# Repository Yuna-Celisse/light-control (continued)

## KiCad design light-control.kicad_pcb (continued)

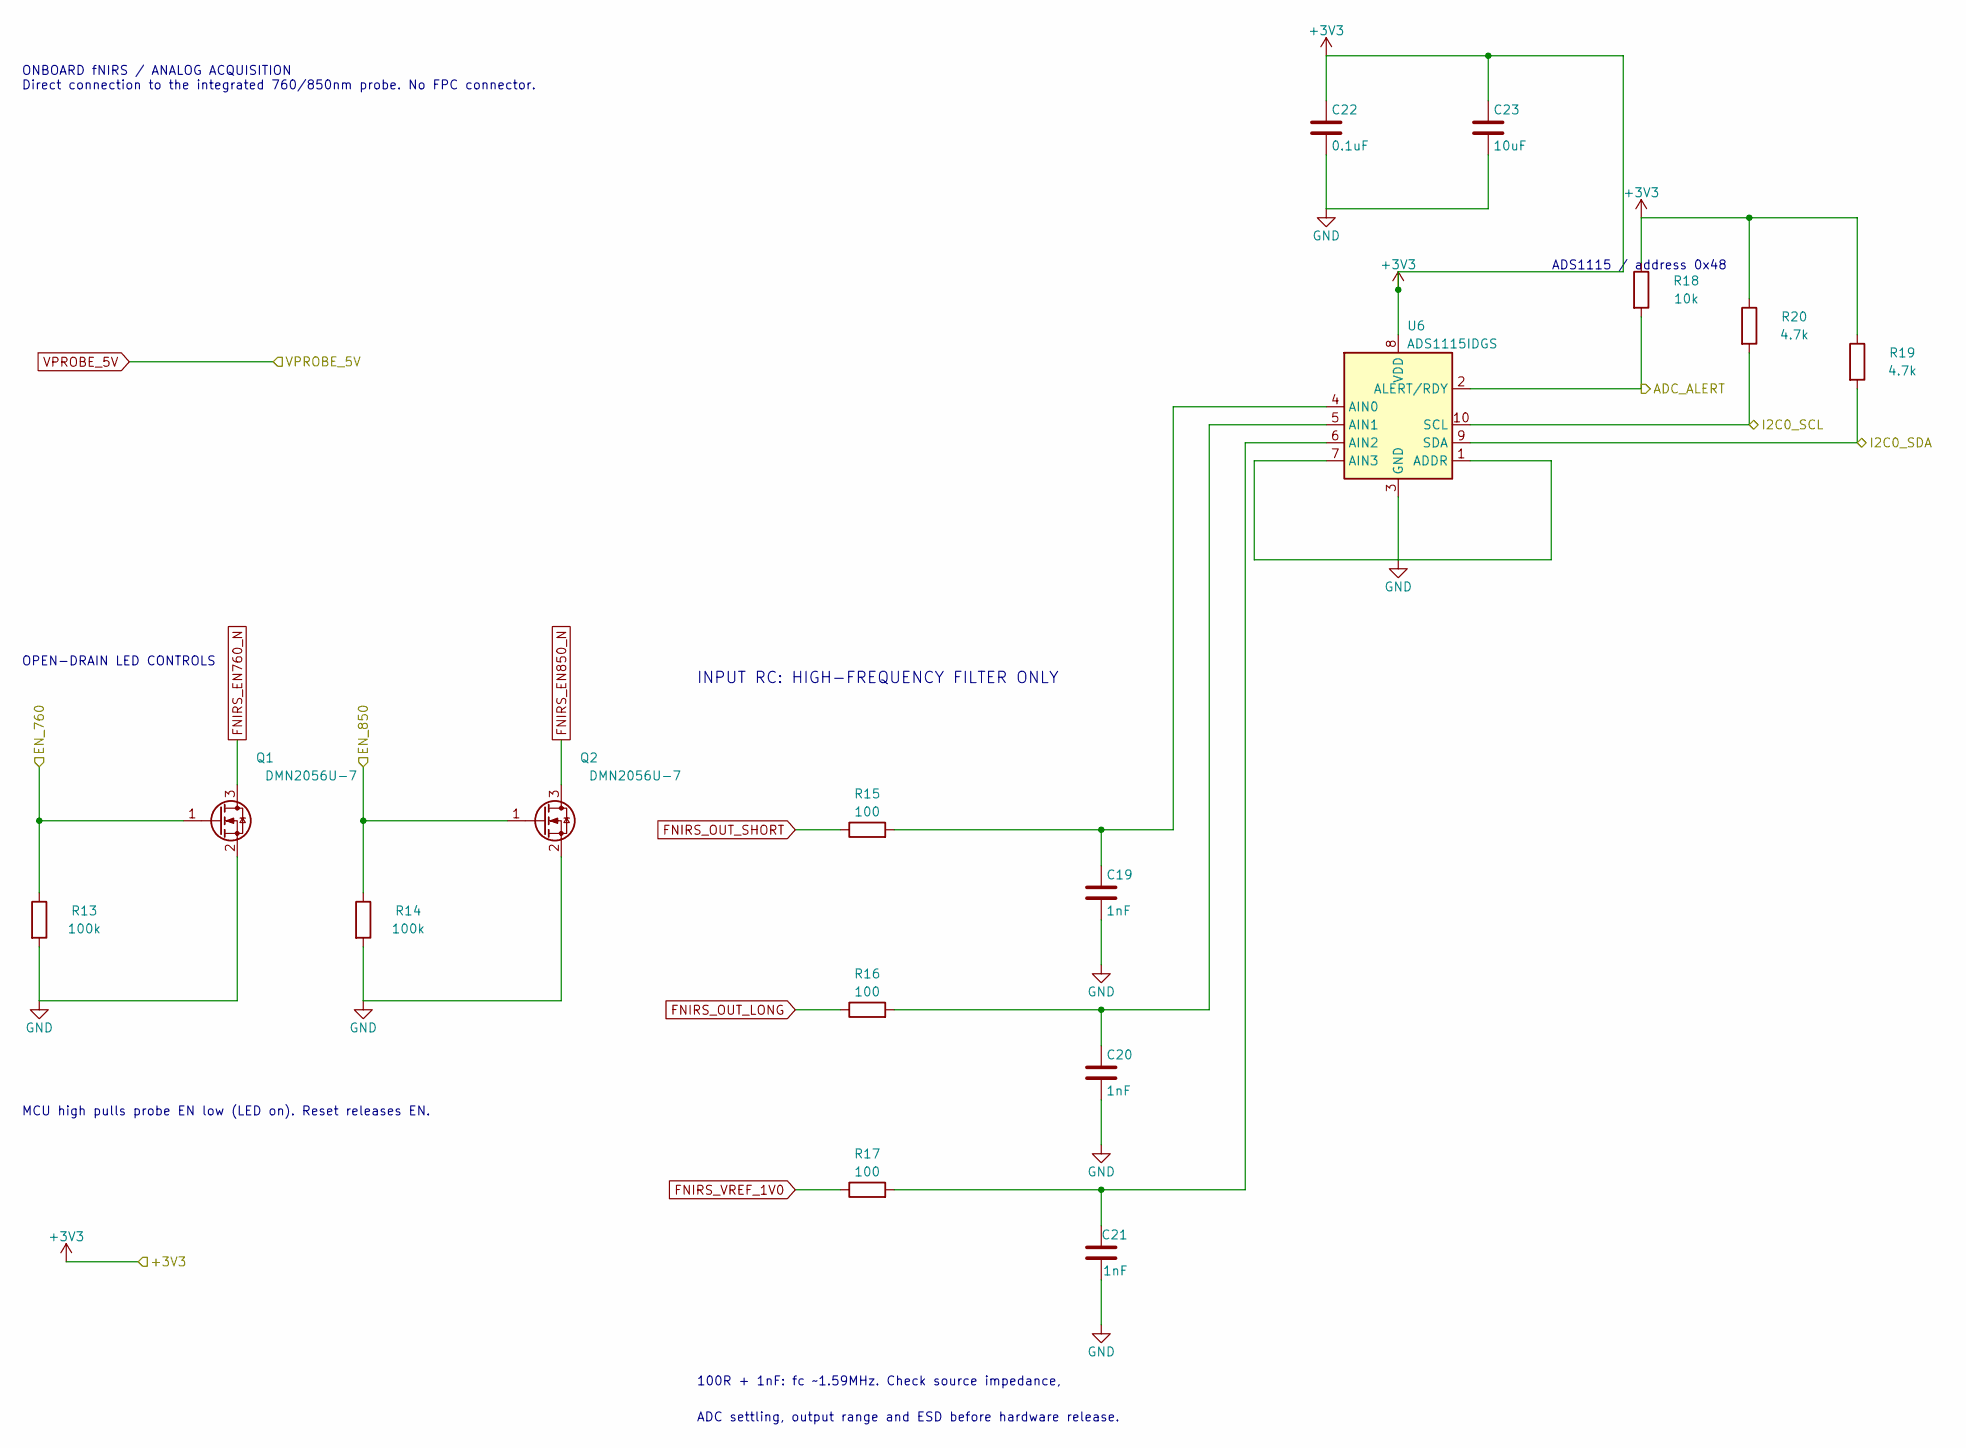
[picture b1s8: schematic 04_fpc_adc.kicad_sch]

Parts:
C19, C20, C21: 1nF; C_0402_1005Metric
C22: 0.1uF; C_0402_1005Metric
C23: 10uF; C_0805_2012Metric
Q1, Q2: DMN2056U-7; SOT-23; MPN DMN2056U-7
R13, R14: 100k; R_0402_1005Metric
R15, R16, R17: 100; R_0402_1005Metric
R18: 10k; R_0402_1005Metric
R19, R20: 4.7k; R_0402_1005Metric
U6: ADS1115IDGS; TSSOP-10_3x3mm_P0.5mm; MPN ADS1115IDGS

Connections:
+3V3: C22.1, C23.1, R18.1, R19.1, R20.1, U6.8 (VDD); also elsewhere on the board
/ADC_ALERT: R18.2, U6.2 (ALERT/RDY); also elsewhere on the board
/EN_760: Q1.1 (G), R13.1; also elsewhere on the board
/EN_850: Q2.1 (G), R14.1; also elsewhere on the board
/I2C0_SCL: R20.2, U6.10 (SCL); also elsewhere on the board
/I2C0_SDA: R19.2, U6.9 (SDA); also elsewhere on the board
FNIRS_EN760_N: Q1.3 (D); also elsewhere on the board
FNIRS_EN850_N: Q2.3 (D); also elsewhere on the board
FNIRS_OUT_LONG: R16.1; also elsewhere on the board
FNIRS_OUT_SHORT: R15.1; also elsewhere on the board
FNIRS_VREF_1V0: R17.1; also elsewhere on the board
unnamed: C19.1, R15.2, U6.4 (AIN0)
unnamed: C20.1, R16.2, U6.5 (AIN1)
unnamed: C21.2, R17.2, U6.6 (AIN2)

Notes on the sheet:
ADC settling, output range and ESD before hardware release.
ADS1115 / address 0x48
100R + 1nF: fc ~1.59MHz. Check source impedance,
INPUT RC: HIGH-FREQUENCY FILTER ONLY
MCU high pulls probe EN low (LED on). Reset releases EN.
ONBOARD fNIRS / ANALOG ACQUISITION Direct connection to the integrated 760/850nm probe. No FPC connector.
OPEN-DRAIN LED CONTROLS

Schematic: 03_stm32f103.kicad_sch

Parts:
C15: 10uF; C_0805_2012Metric
C16, C17, C18, C33, C35, C37: 100nF; C_0402_1005Metric
C34: 1uF; C_0402_1005Metric
C38, C39: 6pF C0G; C_0402_1005Metric
D1: LED_STATE; LED_0603_1608Metric
J2: SWD_PADS; SWD_SolderPads_1x06_P2.00mm
R9, R11, R12, R41: 10k; R_0402_1005Metric
R10: 1k; R_0402_1005Metric
R36, R37: 22; R_0402_1005Metric
R42: 1.5k; R_0402_1005Metric
SW1: RESET; SW_SPST_PTS645Sx43SMTR92
SW2: USER_KEY; SW_SPST_PTS645Sx43SMTR92
SW3: BOOT; SW_SPST_PTS645Sx43SMTR92
TP1: USART1_RX; TestPoint_Pad_D1.0mm
TP2: USART1_TX; TestPoint_Pad_D1.0mm
U5: STM32F103C8T6; LQFP-48_7x7mm_P0.5mm
Y1: ABM8W-12.0000MHZ-6-D1X-T3; Crystal_SMD_3225-4Pin_3.2x2.5mm; MPN ABM8W-12.0000MHZ-6-D1X-T3

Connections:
+3V3: C15.1, C16.1, C17.1, C33.1, C34.1, C35.1, C37.1, J2.1, R9.1, R11.1, R42.1, SW3.2, U5.1 (VBAT), U5.9 (VDDA), U5.24 (VDD), U5.36 (VDD), U5.48 (VDD); also elsewhere on the board
/03_STM32F103/LED_DRV: R10.1, U5.45 (PB8)
/03_STM32F103/NRST: C18.1, J2.5, R9.2, SW1.1, U5.7 (NRST)
/03_STM32F103/SWCLK: J2.4, U5.37 (PA14)
/03_STM32F103/SWDIO: J2.2, U5.34 (PA13)
/03_STM32F103/USART1_RX: TP1.1 (Pin_1_1), U5.31 (PA10)
/03_STM32F103/USART1_TX: TP2.1 (Pin_1_1), U5.30 (PA9)
/03_STM32F103/USER_KEY: R11.2, SW2.1, U5.12 (PA2)
/ADC_ALERT: U5.19 (PB1); also elsewhere on the board
/AS7341_L_INT: U5.25 (PB12); also elsewhere on the board
/AS7341_R_INT: U5.26 (PB13); also elsewhere on the board
/EN_760: U5.10 (PA0); also elsewhere on the board
/EN_850: U5.11 (PA1); also elsewhere on the board
/I2C0_SCL: U5.42 (PB6); also elsewhere on the board
/I2C0_SDA: U5.43 (PB7); also elsewhere on the board
/I2C1_SCL: U5.21 (PB10); also elsewhere on the board
/I2C1_SDA: U5.22 (PB11); also elsewhere on the board
/PROBE_EN: U5.18 (PB0); also elsewhere on the board
/USB_D+: R37.1; also elsewhere on the board
/USB_D-: R36.1; also elsewhere on the board
/VBUS_DET: U5.13 (PA3); also elsewhere on the board
unnamed: D1.2 (A), R10.2
unnamed: R12.1, SW3.1, U5.44 (BOOT0)
unnamed: R36.2, U5.32 (PA11)
unnamed: R37.2, R42.2, U5.33 (PA12)
unnamed: R41.1, U5.20 (PB2)
unnamed: C38.1, U5.5 (PD0), Y1.1
unnamed: C39.1, U5.6 (PD1), Y1.3

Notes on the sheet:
VDD24 / VDD36 / VDD48: 100nF each; VBAT: 100nF; VDDA: 100nF + 1uF
BOOT0 normally LOW; press BOOT then RESET for USART1 ROM loader
Y1 production selection: ABM8W 12MHz CL6pF. PLL x6 ->72MHz, USB /1.5 ->48MHz.
I2C1 PB6/7 -> ADC + AS7341 left; I2C2 PB10/11 -> AS7341 right
C38/C39=6pF initial. CL=3pF + assumed PCB stray3pF; tune after final PCB.
SWD J2: 1=VTref 2=SWDIO 3=GND 4=SWCLK 5=NRST 6=GND
STM32F103C8T6 / 72MHz / USB FS

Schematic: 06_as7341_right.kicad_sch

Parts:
C28, C29, C31: 0.1uF; C_0402_1005Metric
C30: 1uF; C_0402_1005Metric
Q4: DMN2056U-7; SOT-23; MPN DMN2056U-7
R29, R30, R31, R32: 4.7k; R_0402_1005Metric
R33: 200k; R_0402_1005Metric; Tolerance 1%
R34, R35: 10k; R_0402_1005Metric
U9: PCA9306DCUR; VSSOP-8_2.3x2mm_P0.5mm; MPN PCA9306DCUR
U10: AS7341-DLGT; AMS_OLGA-8_2x3.1mm_P0.8mm; MPN AS7341-DLGT

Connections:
+1V8: C28.1, C30.1, C31.1, Q4.1 (G), R29.1, R30.1, R34.2, U9.2 (VREF1), U10.1 (VDD); also elsewhere on the board
+3V3: R31.1, R32.1, R33.1, R35.2; also elsewhere on the board
/AS7341_R_INT: Q4.3 (D), R35.1; also elsewhere on the board
/I2C1_SCL: R32.2, U9.6 (SCL2); also elsewhere on the board
/I2C1_SDA: R31.2, U9.5 (SDA2); also elsewhere on the board
unnamed: Q4.2 (S), R34.1, U10.7 (INT)
unnamed: C29.1, R33.2, U9.7 (VREF2), U9.8 (EN)
unnamed: R29.2, U9.3 (SCL1), U10.2 (SCL)
unnamed: R30.2, U9.4 (SDA1), U10.8 (SDA)

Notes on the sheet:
PCA9306 bias: EN = VREF2; 200k to 3V3
DMN2056U-7: Rds(on) specified at Vgs=1.5V.
1.8V -> 3.3V OPEN-DRAIN INTERRUPT
RIGHT AS7341 / 1.8V OPTICAL SENSOR
1V8 common 68k bleed is on power sheet.
LDR / GPIO unused. Keep optical aperture clear.

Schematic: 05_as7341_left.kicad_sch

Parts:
C24, C25, C27: 0.1uF; C_0402_1005Metric
C26: 1uF; C_0402_1005Metric
Q3: DMN2056U-7; SOT-23; MPN DMN2056U-7
R21, R22, R23, R24: 4.7k; R_0402_1005Metric
R25: 200k; R_0402_1005Metric; Tolerance 1%
R26, R27: 10k; R_0402_1005Metric
U7: PCA9306DCUR; VSSOP-8_2.3x2mm_P0.5mm; MPN PCA9306DCUR
U8: AS7341-DLGT; AMS_OLGA-8_2x3.1mm_P0.8mm; MPN AS7341-DLGT

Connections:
+1V8: C24.1, C26.1, C27.1, Q3.1 (G), R21.1, R22.1, R26.2, U7.2 (VREF1), U8.1 (VDD); also elsewhere on the board
+3V3: R23.1, R24.1, R25.1, R27.2; also elsewhere on the board
/AS7341_L_INT: Q3.3 (D), R27.1; also elsewhere on the board
/I2C0_SCL: R24.2, U7.6 (SCL2); also elsewhere on the board
/I2C0_SDA: R23.2, U7.5 (SDA2); also elsewhere on the board
unnamed: Q3.2 (S), R26.1, U8.7 (INT)
unnamed: C25.1, R25.2, U7.7 (VREF2), U7.8 (EN)
unnamed: R21.2, U7.3 (SCL1), U8.2 (SCL)
unnamed: R22.2, U7.4 (SDA1), U8.8 (SDA)

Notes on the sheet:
LDR / GPIO unused. Keep optical aperture clear.
1.8V -> 3.3V OPEN-DRAIN INTERRUPT
DMN2056U-7: Rds(on) specified at Vgs=1.5V.
PCA9306 bias: EN = VREF2; 200k to 3V3
1V8 common 68k bleed is on power sheet.
LEFT AS7341 / 1.8V OPTICAL SENSOR

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
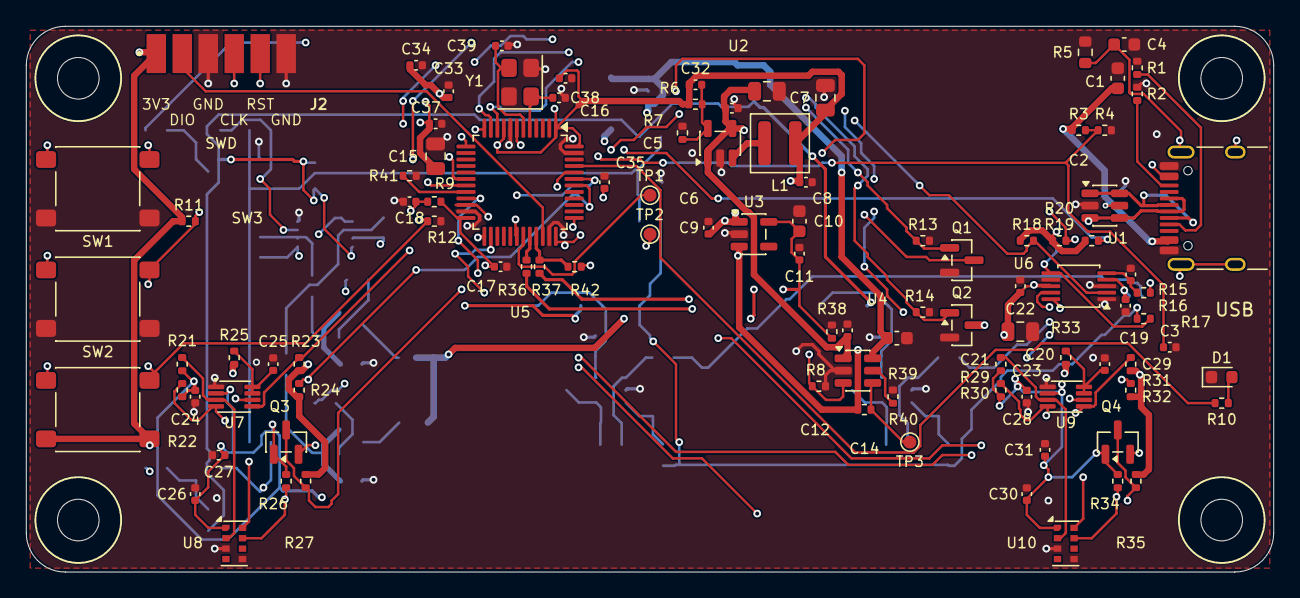
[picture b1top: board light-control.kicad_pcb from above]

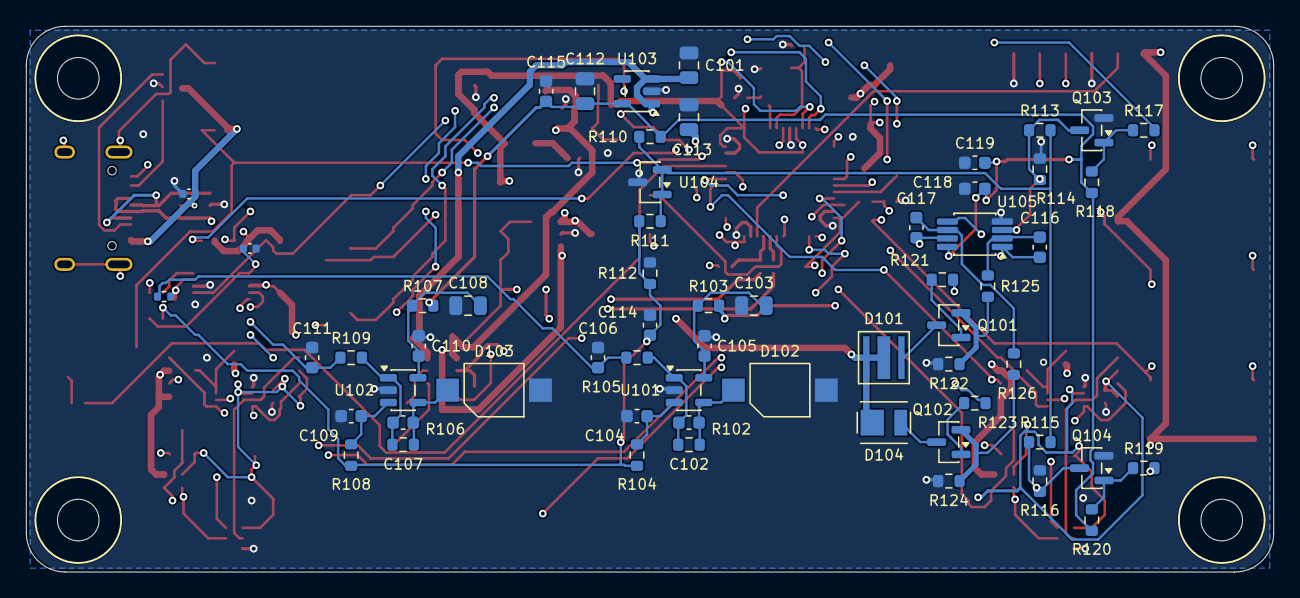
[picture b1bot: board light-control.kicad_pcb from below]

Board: 4 copper layers, 96.0 x 42.0 mm, 164 parts (60 on the bottom side), 79 nets.

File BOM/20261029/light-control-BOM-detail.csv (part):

"Reference","Value","Footprint","Quantity","Manufacturer","MPN","Tolerance","Dielectric","ProcurementStatus","Datasheet","DNP","ExcludeFromBOM","ExcludeFromBoard"
"C1","1uF_16V","Capacitor_SMD:C_0603_1608Metric","1","","","","","","","","",""
"C2","0.1uF","Capacitor_SMD:C_0402_1005Metric","1","","","","","","","","",""
"C3","10nF","Capacitor_SMD:C_0402_1005Metric","1","","","","","","","","",""
"C4","10nF","Capacitor_SMD:C_0603_1608Metric","1","","","","","","","","",""
"C5","4.7uF_16V","Capacitor_SMD:C_0805_2012Metric","1","","","","","","","","",""
"C6","0.1uF","Capacitor_SMD:C_0402_1005Metric","1","","","","","","","","",""
"C7","22uF_10V","Capacitor_SMD:C_0805_2012Metric","1","","","","","","","","",""
"C8","0.1uF","Capacitor_SMD:C_0402_1005Metric","1","","","","","","","","",""
"C9","1uF","Capacitor_SMD:C_0402_1005Metric","1","","","","","","","","",""
"C10","2.2uF","Capacitor_SMD:C_0603_1608Metric","1","","","","","","","","",""
"C11","0.1uF","Capacitor_SMD:C_0402_1005Metric","1","","","","","","","","",""
"C12","1uF_16V","Capacitor_SMD:C_0402_1005Metric","1","","","","","","","","",""
"C14","4.7uF","Capacitor_SMD:C_0603_1608Metric","1","","","","","","","","",""
"C15","10uF","Capacitor_SMD:C_0805_2012Metric","1","","","","","","","","",""
"C16","100nF","Capacitor_SMD:C_0402_1005Metric","1","","","","","","","","",""
"C17","100nF","Capacitor_SMD:C_0402_1005Metric","1","","","","","","","","",""
"C18","1uF","Capacitor_SMD:C_0402_1005Metric","1","","","","","","","","",""
"C19","1nF","Capacitor_SMD:C_0402_1005Metric","1","","","","","","","","",""
"C20","1nF","Capacitor_SMD:C_0402_1005Metric","1","","","","","","","","",""
"C21","1nF","Capacitor_SMD:C_0402_1005Metric","1","","","","","","","","",""
"C22","0.1uF","Capacitor_SMD:C_0402_1005Metric","1","","","","","","","","",""
"C23","10uF","Capacitor_SMD:C_0805_2012Metric","1","","","","","","","","",""
"C24","0.1uF","Capacitor_SMD:C_0402_1005Metric","1","","","","","","","","",""
"C25","0.1uF","Capacitor_SMD:C_0402_1005Metric","1","","","","","","","","",""
"C26","1uF","Capacitor_SMD:C_0402_1005Metric","1","","","","","","","","",""
"C27","0.1uF","Capacitor_SMD:C_0402_1005Metric","1","","","","","","","","",""
"C28","0.1uF","Capacitor_SMD:C_0402_1005Metric","1","","","","","","","","",""
"C29","0.1uF","Capacitor_SMD:C_0402_1005Metric","1","","","","","","","","",""
"C30","1uF","Capacitor_SMD:C_0402_1005Metric","1","","","","","","","","",""
"C31","0.1uF","Capacitor_SMD:C_0402_1005Metric","1","","","","","","","","",""
"C32","6.8pF","Capacitor_SMD:C_0402_1005Metric","1","","","5%","C0G","","","","",""
"C33","100nF","Capacitor_SMD:C_0402_1005Metric","1","","","","","","","","",""
"C34","1uF","Capacitor_SMD:C_0402_1005Metric","1","","","","","","","","",""
"C35","100nF","Capacitor_SMD:C_0402_1005Metric","1","","","","","","","","",""
"C36","1uF","Capacitor_SMD:C_0402_1005Metric","1","","","","","","","","",""
"C37","100nF","Capacitor_SMD:C_0402_1005Metric","1","","","","","","","","",""
"C38","15pF C0G","Capacitor_SMD:C_0402_1005Metric","1","","","","","","","","",""
"C39","15pF C0G","Capacitor_SMD:C_0402_1005Metric","1","","","","","","","","",""
"C101","10uF","Capacitor_SMD:C_0805_2012Metric","1","","CL21A106KAYNNNE","","","","","","",""
"C102","10pF","Capacitor_SMD:C_0603_1608Metric","1","SAMSUNG(三星)","CL10C100JB8NNNC","","","","","","",""
"C103","10uF","Capacitor_SMD:C_0805_2012Metric","1","","CL21A106KAYNNNE","","","","","","",""
"C104","1uF","Capacitor_SMD:C_0603_1608Metric","1","SAMSUNG(三星)","CL10A105KB8NNNC","","","","","","",""
"C105","100nF","Capacitor_SMD:C_0603_1608Metric","1","YAGEO(国巨)","CC0603KRX7R9BB104","","","","","","",""
"C106","10nF","Capacitor_SMD:C_0603_1608Metric","1","FH(风华)","0603B103K500NT","","","","","","",""
"C107","1.5pF","Capacitor_SMD:C_0603_1608Metric","1","SAMSUNG(三星)","CL10C1R5BB8NNNC","","","","","","",""
"C108","10uF","Capacitor_SMD:C_0805_2012Metric","1","","CL21A106KAYNNNE","","","","","","",""
"C109","1uF","Capacitor_SMD:C_0603_1608Metric","1","SAMSUNG(三星)","CL10A105KB8NNNC","","","","","","",""
"C110","100nF","Capacitor_SMD:C_0603_1608Metric","1","YAGEO(国巨)","CC0603KRX7R9BB104","","","","","","",""
"C111","10nF","Capacitor_SMD:C_0603_1608Metric","1","FH(风华)","0603B103K500NT","","","","","","",""
"C112","10uF","Capacitor_SMD:C_0805_2012Metric","1","","CL21A106KAYNNNE","","","","","","",""
"C113","10uF","Capacitor_SMD:C_0805_2012Metric","1","","CL21A106KAYNNNE","","","","","","",""
"C114","1uF","Capacitor_SMD:C_0603_1608Metric","1","SAMSUNG(三星)","CL10A105KB8NNNC","","","","","","",""
"C115","100nF","Capacitor_SMD:C_0603_1608Metric","1","SAMSUNG(三星)","CL10B104KB8NNNC","","","","","","",""
"C116","1nF","Capacitor_SMD:C_0603_1608Metric","1","SAMSUNG(三星)","CL10C102JB8NNNC","","","","","","",""
"C117","1nF","Capacitor_SMD:C_0603_1608Metric","1","SAMSUNG(三星)","CL10C102JB8NNNC","","","","","","",""
"C118","100nF","Capacitor_SMD:C_0603_1608Metric","1","","","","","","","","",""
"C119","1uF","Capacitor_SMD:C_0603_1608Metric","1","","","","","","","","",""
"D1","LED_STATE","LED_SMD:LED_0603_1608Metric","1","","","","","","","","",""
"D101","760-770nm","FNIRS:JNJ_760_3535_3P","1","JNJOPTO(强生光电)","JNJ-LEHR0113W120/42MIL/760-770NM","","","","","","",""
"D102","VBPW34S","FNIRS:VBPW34S_Normal_Gullwing","1","VISHAY(威世)","VBPW34S","","","","","","",""
"D103","VBPW34S","FNIRS:VBPW34S_Normal_Gullwing","1","VISHAY(威世)","VBPW34S","","","","","","",""
"D104","850nm","FNIRS:JNJ_850_3036_2P","1","JNJOPTO(强生光电)","JNJ-LTJI0106W90/14mil-D/850NM","","","","","","",""
"H1","M3_NPTH_3.2mm","Lights_Edge:MountingHole_M3_3.2mm_Clearance7mm","1","","","","","","","","",""
"H2","M3_NPTH_3.2mm","Lights_Edge:MountingHole_M3_3.2mm_Clearance7mm","1","","","","","","","","",""
"H3","M3_NPTH_3.2mm","Lights_Edge:MountingHole_M3_3.2mm_Clearance7mm","1","","","","","","","","",""
"H4","M3_NPTH_3.2mm","Lights_Edge:MountingHole_M3_3.2mm_Clearance7mm","1","","","","","","","","",""
"J1","USB-C_16P","Lights_Edge:USB_C_Receptacle_HRO_TYPE-C-31-M-12","1","","","","","","https://www.usb.org/sites/default/files/documents/usb_type-c.zip","","",""
"L1","XAL4020-222MEC","Inductor_SMD:L_Coilcraft_XAL4020-XXX","1","","","","","","","","",""
"L2","2nH 600mA","Inductor_SMD:L_0402_1005Metric","1","","","","","","","","",""
"L3","24nH","Inductor_SMD:L_0402_1005Metric","1","","","","","","","","",""
"Q1","DMN2056U-7","Package_TO_SOT_SMD:SOT-23","1","Diodes Incorporated","DMN2056U-7","","","","https://www.diodes.com/assets/Datasheets/DMN2056U.pdf","","",""
"Q2","DMN2056U-7","Package_TO_SOT_SMD:SOT-23","1","Diodes Incorporated","DMN2056U-7","","","","https://www.diodes.com/assets/Datasheets/DMN2056U.pdf","","",""
"Q3","DMN2056U-7","Package_TO_SOT_SMD:SOT-23","1","Diodes Incorporated","DMN2056U-7","","","","https://www.diodes.com/assets/Datasheets/DMN2056U.pdf","","",""
"Q4","DMN2056U-7","Package_TO_SOT_SMD:SOT-23","1","Diodes Incorporated","DMN2056U-7","","","","https://www.diodes.com/assets/Datasheets/DMN2056U.pdf","","",""
"Q101","AO3400A","Package_TO_SOT_SMD:SOT-23","1","Alpha and Omega Semiconductor","AO3400A","","","","http://www.aosmd.com/pdfs/datasheet/AO3400A.pdf","","",""
"Q102","AO3400A","Package_TO_SOT_SMD:SOT-23","1","Alpha and Omega Semiconductor","AO3400A","","","","http://www.aosmd.com/pdfs/datasheet/AO3400A.pdf","","",""
"Q103","2N7002","Package_TO_SOT_SMD:SOT-23","1","Vishay","2N7002","","","","https://www.onsemi.com/pub/Collateral/NDS7002A-D.PDF","","",""
"Q104","2N7002","Package_TO_SOT_SMD:SOT-23","1","Vishay","2N7002","","","","https://www.onsemi.com/pub/Collateral/NDS7002A-D.PDF","","",""
"R1","5.1k","Resistor_SMD:R_0402_1005Metric","1","","","","","","","","",""
"R2","5.1k","Resistor_SMD:R_0402_1005Metric","1","","","","","","","","",""
"R3","100k","Resistor_SMD:R_0402_1005Metric","1","","","","","","","","",""
"R4","150k","Resistor_SMD:R_0402_1005Metric","1","","","","","","","","",""
"R5","1M","Resistor_SMD:R_0603_1608Metric","1","","","","","","","","",""
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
